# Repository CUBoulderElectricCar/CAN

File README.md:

# CAN
Everything related to CAN to help with resuability

Notes:  
-All MCUs get their own folder  
-General non-MCU-specific code can go straight into the repo

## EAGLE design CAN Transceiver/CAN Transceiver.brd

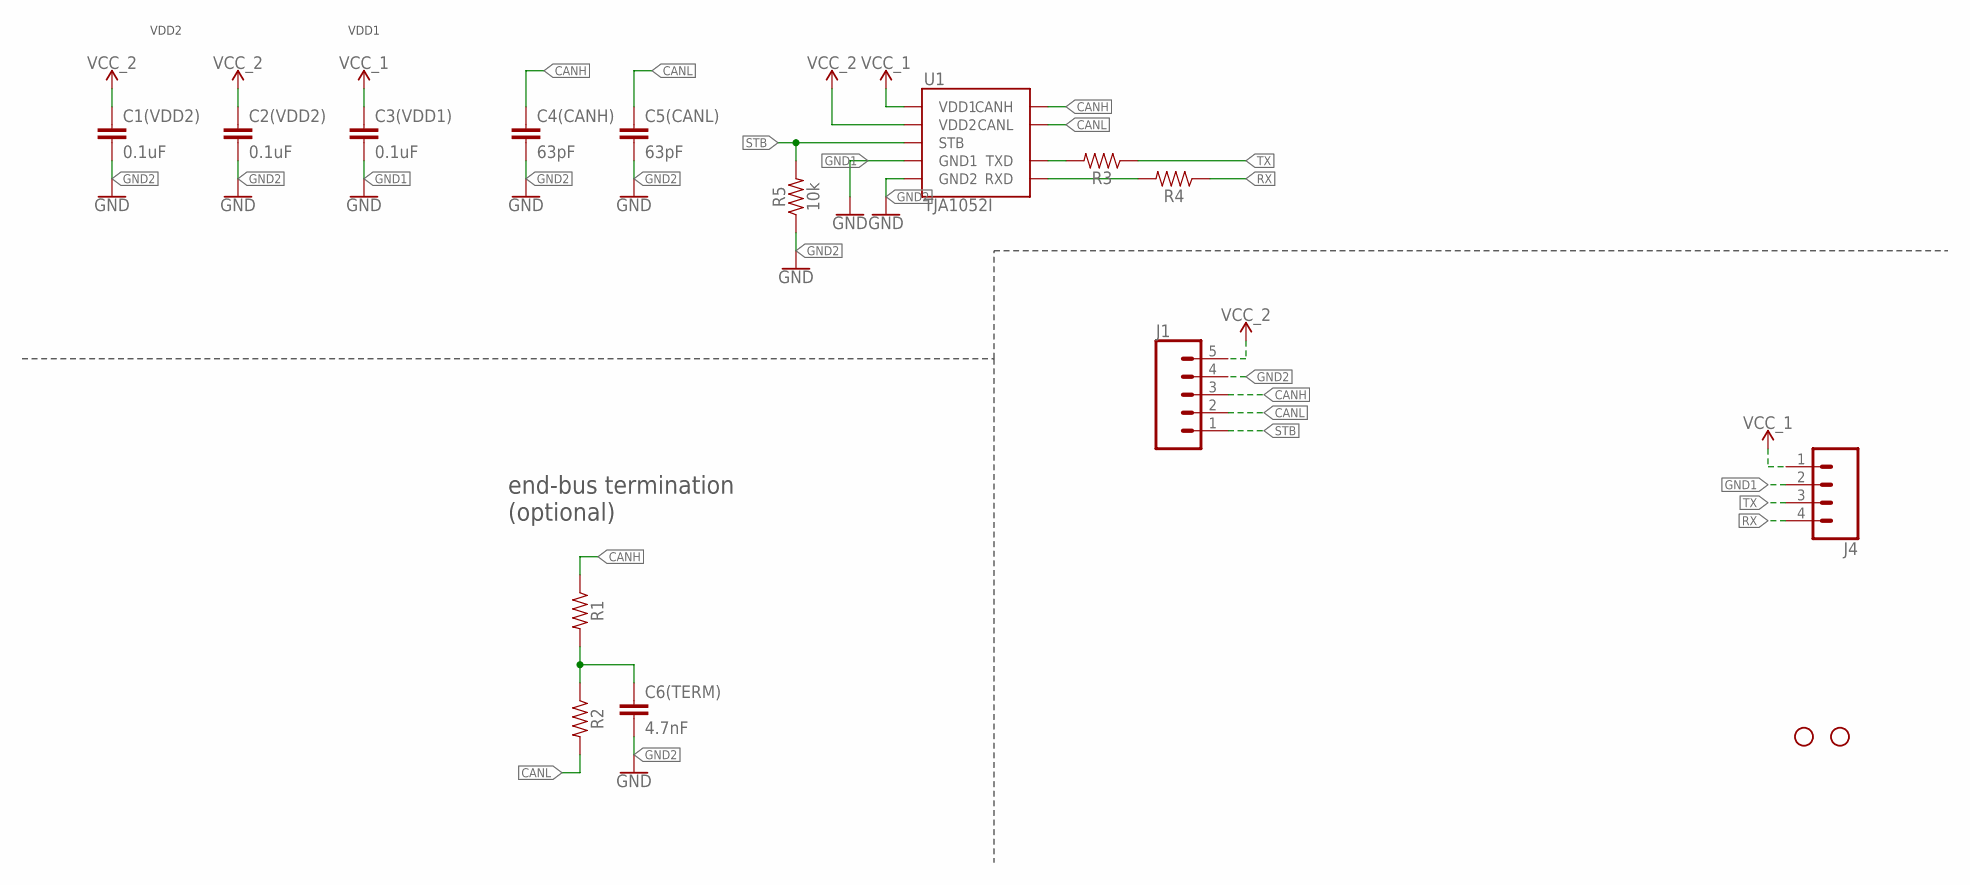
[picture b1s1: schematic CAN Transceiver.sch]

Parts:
C1(VDD2), C2(VDD2), C3(VDD1): 0.1uF; 0603
C4(CANH), C5(CANL): 63pF; 0603
C6(TERM): 4.7nF; 0603
H1, H3: STAND-OFF
J1: CONN_05; 1X05
J4: CONN_04; 1X04
R1, R2, R3, R4: 0603
R5: 10k; 0603
U1: TJA1052I; SO16

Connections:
CANH: C4(CANH).1, J1.3, R1.1, U1.13 (CANH)
CANL: C5(CANL).1, J1.2, R2.2, U1.12 (CANL)
GND1: C3(VDD1).2, J4.2, U1.2 (GND1), U1.7 (GND1), U1.8 (GND1)
GND2: C1(VDD2).2, C2(VDD2).2, C4(CANH).2, C5(CANL).2, C6(TERM).2, J1.4, R5.1, U1.9 (GND2), U1.10 (GND2), U1.15 (GND2)
unnamed: R3.2, U1.3 (TXD)
unnamed: R4.2, U1.5 (RXD)
unnamed: C6(TERM).1, R1.2, R2.1
RX: J4.4, R4.1
STB: J1.1, R5.2, U1.14 (STB)
TX: J4.3, R3.1
VCC_1: C3(VDD1).1, J4.1, U1.1 (VDD1)
VCC_2: C1(VDD2).1, C2(VDD2).1, J1.5, U1.11 (VDD2), U1.16 (VDD2)

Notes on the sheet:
VDD2
VDD1
end-bus termination (optional)

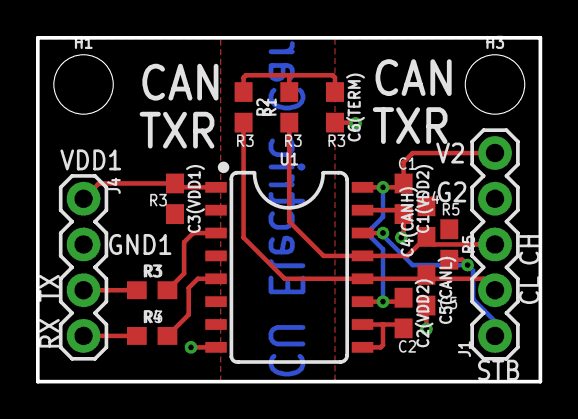
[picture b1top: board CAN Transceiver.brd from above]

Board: 2 copper layers, 27.9 x 19.1 mm, 16 parts (0 on the bottom side), 12 nets.

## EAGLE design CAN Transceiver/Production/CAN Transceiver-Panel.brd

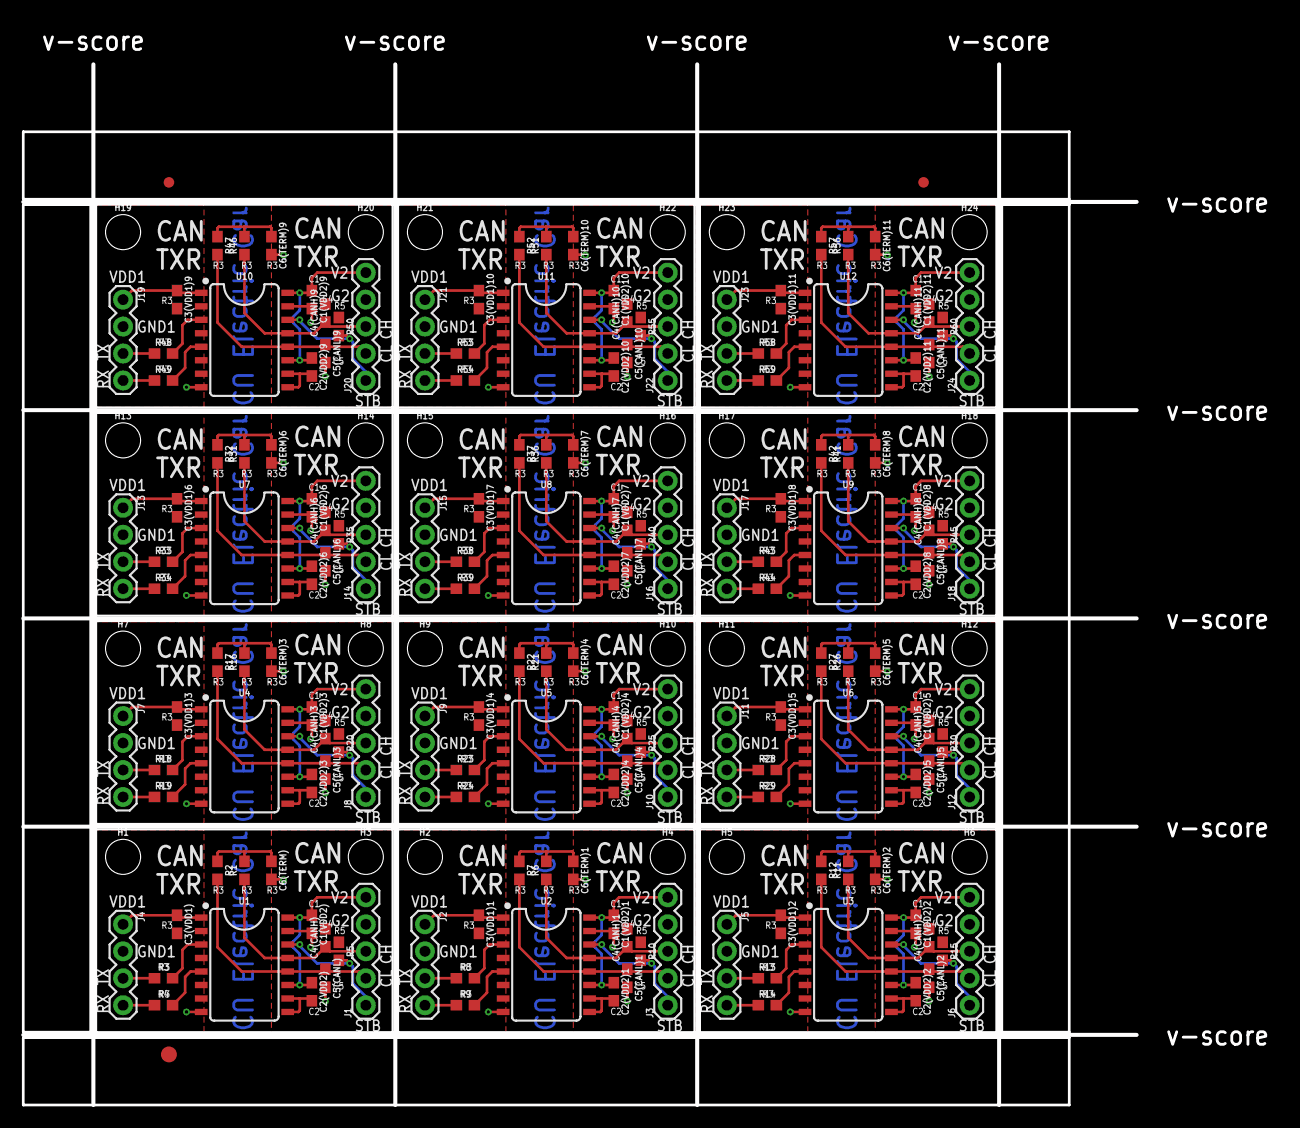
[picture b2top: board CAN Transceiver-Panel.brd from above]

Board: 2 copper layers, 118.0 x 101.9 mm, 195 parts (0 on the bottom side), 144 nets.

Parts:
C1(VDD2), C1(VDD2)1, C1(VDD2)2, C1(VDD2)3, C1(VDD2)4, C1(VDD2)5, C1(VDD2)6, C1(VDD2)7, C1(VDD2)8, C1(VDD2)9, C1(VDD2)10, C1(VDD2)11, C2(VDD2), C2(VDD2)1, C2(VDD2)2, C2(VDD2)3, C2(VDD2)4, C2(VDD2)5, C2(VDD2)6, C2(VDD2)7, C2(VDD2)8, C2(VDD2)9, C2(VDD2)10, C2(VDD2)11, C3(VDD1), C3(VDD1)1, C3(VDD1)2, C3(VDD1)3, C3(VDD1)4, C3(VDD1)5, C3(VDD1)6, C3(VDD1)7, C3(VDD1)8, C3(VDD1)9, C3(VDD1)10, C3(VDD1)11: 0.1uF; 0603
C4(CANH), C4(CANH)1, C4(CANH)2, C4(CANH)3, C4(CANH)4, C4(CANH)5, C4(CANH)6, C4(CANH)7, C4(CANH)8, C4(CANH)9, C4(CANH)10, C4(CANH)11, C5(CANL), C5(CANL)1, C5(CANL)2, C5(CANL)3, C5(CANL)4, C5(CANL)5, C5(CANL)6, C5(CANL)7, C5(CANL)8, C5(CANL)9, C5(CANL)10, C5(CANL)11: 63pF; 0603
C6(TERM), C6(TERM)1, C6(TERM)2, C6(TERM)3, C6(TERM)4, C6(TERM)5, C6(TERM)6, C6(TERM)7, C6(TERM)8, C6(TERM)9, C6(TERM)10, C6(TERM)11: 4.7nF; 0603
E$1, E$2: FIDUCIAL-1X2
E$3: FIDUCIAL-1.5X3
H1, H2, H3, H4, H5, H6, H7, H8, H9, H10, H11, H12, H13, H14, H15, H16, H17, H18, H19, H20, H21, H22, H23, H24: STAND-OFF
J1, J3, J6, J8, J10, J12, J14, J16, J18, J20, J22, J24: 1X05
J2, J4, J5, J7, J9, J11, J13, J15, J17, J19, J21, J23: 1X04
R1, R2, R3, R4, R6, R7, R8, R9, R11, R12, R13, R14, R16, R17, R18, R19, R21, R22, R23, R24, R26, R27, R28, R29, R31, R32, R33, R34, R36, R37, R38, R39, R41, R42, R43, R44, R46, R47, R48, R49, R51, R52, R53, R54, R56, R57, R58, R59: 0603
R5, R10, R15, R20, R25, R30, R35, R40, R45, R50, R55, R60: 10k; 0603
U1, U2, U3, U4, U5, U6, U7, U8, U9, U10, U11, U12: TJA1052I; SO16

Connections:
CANH: C4(CANH).1, J1.3, R1.1, U1.13
CANH1: C4(CANH)1.1, J3.3, R6.1, U2.13
CANH2: C4(CANH)2.1, J6.3, R11.1, U3.13
CANH3: C4(CANH)3.1, J8.3, R16.1, U4.13
CANH4: C4(CANH)4.1, J10.3, R21.1, U5.13
CANH5: C4(CANH)5.1, J12.3, R26.1, U6.13
CANH6: C4(CANH)6.1, J14.3, R31.1, U7.13
CANH7: C4(CANH)7.1, J16.3, R36.1, U8.13
CANH8: C4(CANH)8.1, J18.3, R41.1, U9.13
CANH9: C4(CANH)9.1, J20.3, R46.1, U10.13
CANH10: C4(CANH)10.1, J22.3, R51.1, U11.13
CANH11: C4(CANH)11.1, J24.3, R56.1, U12.13
CANL: C5(CANL).1, J1.2, R2.2, U1.12
CANL1: C5(CANL)1.1, J3.2, R7.2, U2.12
CANL2: C5(CANL)2.1, J6.2, R12.2, U3.12
CANL3: C5(CANL)3.1, J8.2, R17.2, U4.12
CANL4: C5(CANL)4.1, J10.2, R22.2, U5.12
CANL5: C5(CANL)5.1, J12.2, R27.2, U6.12
CANL6: C5(CANL)6.1, J14.2, R32.2, U7.12
CANL7: C5(CANL)7.1, J16.2, R37.2, U8.12
CANL8: C5(CANL)8.1, J18.2, R42.2, U9.12
CANL9: C5(CANL)9.1, J20.2, R47.2, U10.12
CANL10: C5(CANL)10.1, J22.2, R52.2, U11.12
CANL11: C5(CANL)11.1, J24.2, R57.2, U12.12
GND1: C3(VDD1).2, J4.2, U1.2, U1.7, U1.8
GND2: C1(VDD2).2, C2(VDD2).2, C4(CANH).2, C5(CANL).2, C6(TERM).2, J1.4, R5.1, U1.9, U1.10, U1.15
GND3: C1(VDD2)1.2, C2(VDD2)1.2, C4(CANH)1.2, C5(CANL)1.2, C6(TERM)1.2, J3.4, R10.1, U2.9, U2.10, U2.15
GND4: C3(VDD1)1.2, J2.2, U2.2, U2.7, U2.8
GND5: C1(VDD2)2.2, C2(VDD2)2.2, C4(CANH)2.2, C5(CANL)2.2, C6(TERM)2.2, J6.4, R15.1, U3.9, U3.10, U3.15
GND6: C3(VDD1)2.2, J5.2, U3.2, U3.7, U3.8
GND7: C1(VDD2)3.2, C2(VDD2)3.2, C4(CANH)3.2, C5(CANL)3.2, C6(TERM)3.2, J8.4, R20.1, U4.9, U4.10, U4.15
GND8: C3(VDD1)3.2, J7.2, U4.2, U4.7, U4.8
GND9: C1(VDD2)4.2, C2(VDD2)4.2, C4(CANH)4.2, C5(CANL)4.2, C6(TERM)4.2, J10.4, R25.1, U5.9, U5.10, U5.15
GND10: C3(VDD1)4.2, J9.2, U5.2, U5.7, U5.8
GND11: C1(VDD2)5.2, C2(VDD2)5.2, C4(CANH)5.2, C5(CANL)5.2, C6(TERM)5.2, J12.4, R30.1, U6.9, U6.10, U6.15
GND12: C3(VDD1)5.2, J11.2, U6.2, U6.7, U6.8
GND13: C1(VDD2)6.2, C2(VDD2)6.2, C4(CANH)6.2, C5(CANL)6.2, C6(TERM)6.2, J14.4, R35.1, U7.9, U7.10, U7.15
GND14: C3(VDD1)6.2, J13.2, U7.2, U7.7, U7.8
GND15: C1(VDD2)7.2, C2(VDD2)7.2, C4(CANH)7.2, C5(CANL)7.2, C6(TERM)7.2, J16.4, R40.1, U8.9, U8.10, U8.15
GND16: C3(VDD1)7.2, J15.2, U8.2, U8.7, U8.8
GND17: C1(VDD2)8.2, C2(VDD2)8.2, C4(CANH)8.2, C5(CANL)8.2, C6(TERM)8.2, J18.4, R45.1, U9.9, U9.10, U9.15
GND18: C3(VDD1)8.2, J17.2, U9.2, U9.7, U9.8
GND19: C1(VDD2)9.2, C2(VDD2)9.2, C4(CANH)9.2, C5(CANL)9.2, C6(TERM)9.2, J20.4, R50.1, U10.9, U10.10, U10.15
GND20: C3(VDD1)9.2, J19.2, U10.2, U10.7, U10.8
GND21: C1(VDD2)10.2, C2(VDD2)10.2, C4(CANH)10.2, C5(CANL)10.2, C6(TERM)10.2, J22.4, R55.1, U11.9, U11.10, U11.15
GND22: C3(VDD1)10.2, J21.2, U11.2, U11.7, U11.8
GND23: C1(VDD2)11.2, C2(VDD2)11.2, C4(CANH)11.2, C5(CANL)11.2, C6(TERM)11.2, J24.4, R60.1, U12.9, U12.10, U12.15
GND24: C3(VDD1)11.2, J23.2, U12.2, U12.7, U12.8
unnamed: R3.2, U1.3
unnamed: R4.2, U1.5
unnamed: C6(TERM).1, R1.2, R2.1
unnamed: R8.2, U2.3
unnamed: R9.2, U2.5
unnamed: C6(TERM)1.1, R6.2, R7.1
unnamed: R13.2, U3.3
unnamed: R14.2, U3.5
unnamed: C6(TERM)2.1, R11.2, R12.1
unnamed: R18.2, U4.3
unnamed: R19.2, U4.5
unnamed: C6(TERM)3.1, R16.2, R17.1
unnamed: R23.2, U5.3
unnamed: R24.2, U5.5
unnamed: C6(TERM)4.1, R21.2, R22.1
unnamed: R28.2, U6.3
unnamed: R29.2, U6.5
unnamed: C6(TERM)5.1, R26.2, R27.1
unnamed: R33.2, U7.3
unnamed: R34.2, U7.5
unnamed: C6(TERM)6.1, R31.2, R32.1
unnamed: R38.2, U8.3
unnamed: R39.2, U8.5
unnamed: C6(TERM)7.1, R36.2, R37.1
unnamed: R43.2, U9.3
unnamed: R44.2, U9.5
unnamed: C6(TERM)8.1, R41.2, R42.1
unnamed: R48.2, U10.3
unnamed: R49.2, U10.5
unnamed: C6(TERM)9.1, R46.2, R47.1
unnamed: R53.2, U11.3
unnamed: R54.2, U11.5
unnamed: C6(TERM)10.1, R51.2, R52.1
unnamed: R58.2, U12.3
unnamed: R59.2, U12.5
unnamed: C6(TERM)11.1, R56.2, R57.1
RX: J4.4, R4.1
RX1: J2.4, R9.1
RX2: J5.4, R14.1
RX3: J7.4, R19.1
RX4: J9.4, R24.1
RX5: J11.4, R29.1
RX6: J13.4, R34.1
RX7: J15.4, R39.1
RX8: J17.4, R44.1
RX9: J19.4, R49.1
RX10: J21.4, R54.1
RX11: J23.4, R59.1
STB: J1.1, R5.2, U1.14
STB1: J3.1, R10.2, U2.14
STB2: J6.1, R15.2, U3.14
STB3: J8.1, R20.2, U4.14
STB4: J10.1, R25.2, U5.14
STB5: J12.1, R30.2, U6.14
STB6: J14.1, R35.2, U7.14
STB7: J16.1, R40.2, U8.14
STB8: J18.1, R45.2, U9.14
STB9: J20.1, R50.2, U10.14
STB10: J22.1, R55.2, U11.14
STB11: J24.1, R60.2, U12.14
TX: J4.3, R3.1
TX1: J2.3, R8.1
TX2: J5.3, R13.1
TX3: J7.3, R18.1
TX4: J9.3, R23.1
TX5: J11.3, R28.1
TX6: J13.3, R33.1
TX7: J15.3, R38.1
TX8: J17.3, R43.1
TX9: J19.3, R48.1
TX10: J21.3, R53.1
TX11: J23.3, R58.1
VCC_1: C3(VDD1).1, J4.1, U1.1
VCC_2: C1(VDD2).1, C2(VDD2).1, J1.5, U1.11, U1.16
VCC_3: C3(VDD1)1.1, J2.1, U2.1
VCC_4: C1(VDD2)1.1, C2(VDD2)1.1, J3.5, U2.11, U2.16
VCC_5: C3(VDD1)2.1, J5.1, U3.1
VCC_6: C1(VDD2)2.1, C2(VDD2)2.1, J6.5, U3.11, U3.16
VCC_7: C3(VDD1)3.1, J7.1, U4.1
VCC_8: C1(VDD2)3.1, C2(VDD2)3.1, J8.5, U4.11, U4.16
VCC_9: C3(VDD1)4.1, J9.1, U5.1
VCC_10: C1(VDD2)4.1, C2(VDD2)4.1, J10.5, U5.11, U5.16
VCC_11: C3(VDD1)5.1, J11.1, U6.1
VCC_12: C1(VDD2)5.1, C2(VDD2)5.1, J12.5, U6.11, U6.16
VCC_13: C3(VDD1)6.1, J13.1, U7.1
VCC_14: C1(VDD2)6.1, C2(VDD2)6.1, J14.5, U7.11, U7.16
VCC_15: C3(VDD1)7.1, J15.1, U8.1
VCC_16: C1(VDD2)7.1, C2(VDD2)7.1, J16.5, U8.11, U8.16
VCC_17: C3(VDD1)8.1, J17.1, U9.1
VCC_18: C1(VDD2)8.1, C2(VDD2)8.1, J18.5, U9.11, U9.16
VCC_19: C3(VDD1)9.1, J19.1, U10.1
VCC_20: C1(VDD2)9.1, C2(VDD2)9.1, J20.5, U10.11, U10.16
VCC_21: C3(VDD1)10.1, J21.1, U11.1
VCC_22: C1(VDD2)10.1, C2(VDD2)10.1, J22.5, U11.11, U11.16
VCC_23: C3(VDD1)11.1, J23.1, U12.1
VCC_24: C1(VDD2)11.1, C2(VDD2)11.1, J24.5, U12.11, U12.16

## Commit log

2018-06-21 Init configure.h
2018-06-21 Init configureCAN.c
2018-06-21 Rename configureCAN.c to configure.c
2018-06-21 Rename configureCAN.h to configure.h
2018-07-15 production files

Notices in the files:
parts and their libraries:
SparkFun-Capacitors: Licensing: Creative Commons ShareAlike 4.0 International - https://creativecommons.org/licenses/by-sa/4.0
